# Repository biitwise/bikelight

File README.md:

# bikelight
Dynamo bikelight with brakelight

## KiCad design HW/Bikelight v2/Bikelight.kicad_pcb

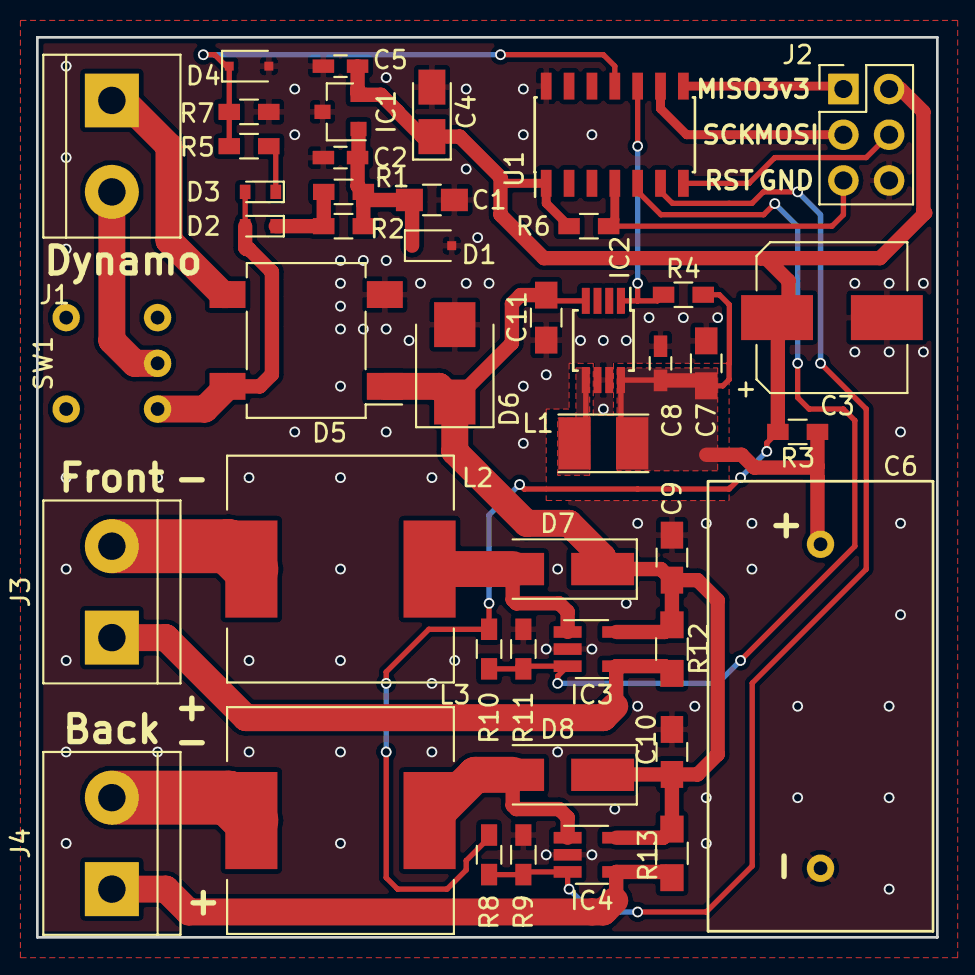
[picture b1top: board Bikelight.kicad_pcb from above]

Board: 2 copper layers, 50.0 x 50.0 mm, 45 parts (0 on the bottom side), 25 nets.

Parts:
C1, C7, C9, C10, C11: 4u7; C_0805_HandSoldering
C2, C5, C8: 100n; C_0603_HandSoldering
C3: EEE-HA1A471UP; CP_Elec_8x10.5
C4: 478-9009-1-ND; CP_Tantalum_Case-A_EIA-3216-18_Reflow
C6: 3F3; SuperCapL25W12.5P18
D1: DDZ8V2ASF-7; D_SOD-323F
D2, D3: TS4148; D_0603
D4: DDZ3V3ASF-7; D_SOD-323F
D5: D_Bridge_+-AA; Diode_Bridge_DFS
D6: SMBJ5346B-TP; D_SMB
D7, D8: D_Schottky; D_SMA_Handsoldering
IC1: RT9058; SOT-23
IC2: MCP1642B; MSOP-8_3x3mm_Pitch0.65mm
IC3, IC4: AL8860WT; SOT-23-5_HandSoldering
J1, J3, J4: Screw_Terminal_1x02; TerminalBlock_bornier-2_P5.08mm
J2: CONN_02X03; Pin_Header_Straight_2x03_Pitch2.54mm
L1: 744025004; L_Taiyo-Yuden_NR-30xx_HandSoldering
L2, L3: 100uH; L_12x12mm_h8mm
R1, R2, R3: 33; R_0603_HandSoldering
R4, R6: 10k; R_0603_HandSoldering
R5: 2k2; R_0603_HandSoldering
R7, R8, R9, R10, R11: 1k; R_0603_HandSoldering
R12: 0.33; R_0805_HandSoldering
R13: 0.58; R_0805_HandSoldering
SW1: 200USP1T1A1M6RE; SW0.2x0.2
U1: ATTINY24A-SSU; SOIC-14_3.9x8.7mm_Pitch1.27mm

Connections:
GND: C1.2, C2.2, C3.2, C4.2, C5.2, C6.2, C7.2, C8.2, C9.2, C10.2, C11.2, D1.2, D4.2, D5.2, D6.2, IC1.3, IC2.6, IC2.7, IC3.2, IC4.2, J2.6, R7.2, R9.2, R11.2, U1.14
unnamed: C1.1, C2.1, D1.1, IC1.1, R1.2, R2.2
unnamed: C3.1, C4.1, C5.1, IC1.2, J2.2, R3.2, R6.1, R8.1, R10.1, U1.1
unnamed: C6.1, C7.1, C8.1, IC2.8, L1.1, R3.1, R4.2
unnamed: C9.1, C10.1, C11.1, D5.1, D6.1, D7.1, D8.1, IC2.4, IC3.5, IC4.5, R12.2, R13.2
unnamed: D2.1, R1.1, R2.1
unnamed: D2.2, D3.2, D5.4, SW1.1
unnamed: D3.1, R5.1
unnamed: D4.1, R5.2, R7.1, U1.11
unnamed: D5.3, J1.1
unnamed: D7.2, IC3.1, L2.2
unnamed: D8.2, IC4.1, L3.2
unnamed: IC2.1, R4.1, U1.10
unnamed: IC2.5, L1.2
unnamed: IC3.3, R10.2, R11.1, U1.5
unnamed: IC3.4, J3.1, R12.1
unnamed: IC4.3, R8.2, R9.1, U1.6
unnamed: IC4.4, J4.1, R13.1
unnamed: J1.2, SW1.2
unnamed: J2.1, U1.8
unnamed: J2.3, U1.9
unnamed: J2.4, U1.7
unnamed: J2.5, R6.2, U1.4
unnamed: J3.2, L2.1
unnamed: J4.2, L3.1

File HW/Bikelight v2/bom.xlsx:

Reference | Quantity no SL | Quantity | Value | Footprint | Teilenummer | Hersteller-Teilenummer | Prize | Total no SL | Total
C3 | 1 | 1 | 470U | Capacitors_SMD:CP_Elec_8x10.5 | EEE-HA1A471UP
C4 | 1 | 1 | 47u | Capacitors_Tantalum_SMD:CP_Tantalum_Case-A_EIA-3216-18_Reflow | 478-9009-1-ND | TLJA476M010R0600 | 0.63 | 0.63 | 0.63
C2 C5 C8 | 3 | 4 | 100n | Capacitors_SMD:C_0603_HandSoldering |  |  |  | 0 | 0
C6 | 0 | 1 | 5F | SCap:SuperCapL25W12.5P18 | 478-10019-ND | SCMT22C505PRBA0 | 5.67 | 0 | 5.67
C1 C7 C9 C10 C11 | 9 | 10 | 4u7 | Capacitors_SMD:C_0805_HandSoldering | 1276-6462-1-ND | CL21A475KAQNNNG | 0.155 | 1.395 | 1.55
D1 | 1 |  | DDZ8V2ASF-7 | Diodes_SMD:D_SOD-323F | DDZ8V2ASF-7
D4 |  |  | DDZ3V3ASF-7 | Diodes_SMD:D_SOD-323F | DDZ3V3ASF-7
D6 |  |  | SMBJ5346B-TP | Diodes_SMD:D_SMB | SMBJ5346B-TP
D2 D3 | 2 | 2 | TS4148C RZG | Diodes_SMD:D_0603 | TS4148CRZGCT-ND | TS4148C RZG | 0.17 | 0.34 | 0.34
D5 | 1 | 1 | D_Bridge_+-AA | Diodes_SMD:Diode_Bridge_DFS | CBRSDSH2-100TR13-CT-ND | CBRSDSH2-100 TR13 | 1.62 | 1.62 | 1.62
D7 D8 | 2 | 2 | D_Schottky | Diodes_SMD:D_SMA_Handsoldering | NRVTSA4100T3GOSCT-ND | NRVTSA4100T3G | 0.42 | 0.84 | 0.84
IC1 | 1 | 1 | RT9058-33GV | TO_SOT_Packages_SMD:SOT-23_Handsoldering | 1028-1253-1-ND | RT9058-33GV | 0.69 | 0.69 | 0.69
IC2 | 0 | 1 | MCP1642B | Housings_SSOP:MSOP-8_3x3mm_Pitch0.65mm | MCP1642B-50I/MS-ND | MCP1642B-50I/MS | 0.98 | 0 | 0.98
IC3 IC4 | 2 | 2 | AL8860WT | TO_SOT_Packages_SMD:SOT-23-5_HandSoldering | AL8860WT-7DICT-ND | AL8860WT-7 | 0.45 | 0.9 | 0.9
J1 J3 J4 | 3 | 3 | Screw_Terminal_1x02 | Connectors_Terminal_Blocks:TerminalBlock_bornier-2_P5.08mm | ED2609-ND | OSTTC022162 | 0.78 | 2.34 | 2.34
J2 | 1 | 1 | CONN_02X03 | Pin_Headers:Pin_Header_Straight_2x03_Pitch2.54mm |  |  |  | 0 | 0
L1 | 0 | 1 | 744025004 | Inductors_SMD:L_Taiyo-Yuden_NR-30xx_HandSoldering | 732-2615-1-ND | 744025004 | 1.49 | 0 | 1.49
L2 L3 | 2 | 2 | 100uH | Inductors_SMD:L_12x12mm_h8mm | SRR1208-101YLCT-ND | SRR1208-101YL | 1.06 | 2.12 | 2.12
 | 0 | 1 | 100 | Resistors_SMD:R_0603_HandSoldering |  |  |  | 0 | 0
 | 1 | 1 | 0.33 | Resistors_SMD:R_0805_HandSoldering | RL12S.33FCT-ND | RL1220S-R33-F | 0.32 | 0.32 | 0.32
 | 1 | 1 | 0.56000000000000005 | Resistors_SMD:R_0805_HandSoldering | RL12S.56FCT-ND | RL1220S-R56-F | 0.32 | 0.32 | 0.32
 | 1 | 3 | 2k2 | Resistors_SMD:R_0603_HandSoldering |  |  |  | 0 | 0
 | 3 | 7 | 1k | Resistors_SMD:R_0603_HandSoldering |  |  |  | 0 | 0
 | 1 | 1 | 100k | Resistors_SMD:R_0603_HandSoldering |  |  |  | 0 | 0
 | 1 | 1 | 10k | Resistors_SMD:R_0603_HandSoldering |  |  |  | 0 | 0
SW1 | 1 | 1 | 200USP1T1A1M6RE |  |  |  |  | 0 | 0
U1 | 1 | 1 | ATTINY24A-SSU | Housings_SOIC:SOIC-14_3.9x8.7mm_Pitch1.27mm | ATTINY24A-SSN-ND | ATTINY24A-SSN | 0.69 | 0.69 | 0.69
 | 1 | 1 | LED XLAMP XPE2 RED STARBOARD |  | 1672-1055-ND | XPEBRD-L1-0000-00901-SB01 | 5.82 | 5.82 | 5.82
 | 1 | 1 | LED MODULE XP-G3 6500K STARBOARD |  | 1672-1091-ND | XPGDWT-01-0000-00LE1-SB01 | 4.99 | 4.99 | 4.99
 | 1 | 1 | LENS CLR 25/34DEG MED ADH TAPE |  | 711-1369-ND | CA15230_VERONICA-SQ-MINI-M | 2.09 | 2.09 | 2.09
 |  |  |  |  |  |  |  | 25.105 | 33.400000000000006

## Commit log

2019-03-26 Wrote C-code based on assembler
2019-09-08 Pulse count version (bugged)
2019-09-08 Pulse length approach for C working, needs filtering
2021-05-24 Introduced hysteresis, in C and asm
